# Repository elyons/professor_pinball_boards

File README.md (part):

These are various PCB designs and Gerber files for various applications in Pinball machines.
# professor_pinball_boards

The .sch and .brd files were generated using Autodesk Eagle PCB CAD software: https://www.autodesk.com/products/eagle/free-download

There are .zip files that can be submitted directly to SEEED Fusion for PCB manufacturing: https://www.seeedstudio.com/fusion.html

All boards are released with the Gnu Public License 3.0: https://www.gnu.org/licenses/gpl-3.0.en.html

---

GNU GENERAL PUBLIC LICENSE

Version 3, 29 June 2007

Copyright © 2007 Free Software Foundation, Inc. <https://fsf.org/>

Everyone is permitted to copy and distribute verbatim copies of this license document, but changing it is not allowed.
Preamble

The GNU General Public License is a free, copyleft license for software and other kinds of works.

The licenses for most software and other practical works are designed to take away your freedom to share and change the works. By contrast, the GNU General Public License is intended to guarantee your freedom to share and change all versions of a program--to make sure it remains free software for all its users. We, the Free Software Foundation, use the GNU General Public License for most of our software; it applies also to any other work released this way by its authors. You can apply it to your programs, too.

When we speak of free software, we are referring to freedom, not price. Our General Public Licenses are designed to make sure that you have the freedom to distribute copies of free software (and charge for them if you wish), that you receive source code or can get it if you want it, that you can change the software or use pieces of it in new free programs, and that you know you can do these things.

To protect your rights, we need to prevent others from denying you these rights or asking you to surrender the rights. Therefore, you have certain responsibilities if you distribute copies of the software, or if you modify it: responsibilities to respect the freedom of others.

For example, if you distribute copies of such a program, whether gratis or for a fee, you must pass on to the recipients the same freedoms that you received. You must make sure that they, too, receive or can get the source code. And you must show them these terms so they know their rights.

Developers that use the GNU GPL protect your rights with two steps: (1) assert copyright on the software, and (2) offer you this License giving you legal permission to copy, distribute and/or modify it.

For the developers' and authors' protection, the GPL clearly explains that there is no warranty for this free software. For both users' and authors' sake, the GPL requires that modified versions be marked as changed, so that their problems will not be attributed erroneously to authors of previous versions.

Some devices are designed to deny users access to install or run modified versions of the software inside them, although the manufacturer can do so. This is fundamentally incompatible with the aim of protecting users' freedom to change the software. The systematic pattern of such abuse occurs in the area of products for individuals to use, which is precisely where it is most unacceptable. Therefore, we have designed this version of the GPL to prohibit the practice for those products. If such problems arise substantially in other domains, we stand ready to extend this provision to those domains in future versions of the GPL, as needed to protect the freedom of users.

Finally, every program is threatened constantly by software patents. States should not allow patents to restrict development and use of software on general-purpose computers, but in those that do, we wish to avoid the special danger that patents applied to a free program could make it effectively proprietary. To prevent this, the GPL assures that patents cannot be used to render the program non-free.

The precise terms and conditions for copying, distribution and modification follow.
TERMS AND CONDITIONS
0. Definitions.

“This License” refers to version 3 of the GNU General Public License.

“Copyright” also means copyright-like laws that apply to other kinds of works, such as semiconductor masks.

“The Program” refers to any copyrightable work licensed under this License. Each licensee is addressed as “you”. “Licensees” and “recipients” may be individuals or organizations.

To “modify” a work means to copy from or adapt all or part of the work in a fashion requiring copyright permission, other than the making of an exact copy. The resulting work is called a “modified version” of the earlier work or a work “based on” the earlier work.

A “covered work” means either the unmodified Program or a work based on the Program.

To “propagate” a work means to do anything with it that, without permission, would make you directly or secondarily liable for infringement under applicable copyright law, except executing it on a computer or modifying a private copy. Propagation includes copying, distribution (with or without modification), making available to the public, and in some countries other activities as well.

To “convey” a work means any kind of propagation that enables other parties to make or receive copies. Mere interaction with a user through a computer network, with no transfer of a copy, is not conveying.

An interactive user interface displays “Appropriate Legal Notices” to the extent that it includes a convenient and prominently visible feature that (1) displays an appropriate copyright notice, and (2) tells the user that there is no warranty for the work (except to the extent that warranties are provided), that licensees may convey the work under this License, and how to view a copy of this License. If the interface presents a list of user commands or options, such as a menu, a prominent item in the list meets this criterion.
1. Source Code.

The “source code” for a work means the preferred form of the work for making modifications to it. “Object code” means any non-source form of a work.

A “Standard Interface” means an interface that either is an official standard defined by a recognized standards body, or, in the case of interfaces specified for a particular programming language, one that is widely used among developers working in that language.

The “System Libraries” of an executable work include anything, other than the work as a whole, that (a) is included in the normal form of packaging a Major Component, but which is not part of that Major Component, and (b) serves only to enable use of the work with that Major Component, or to implement a Standard Interface for which an implementation is available to the public in source code form. A “Major Component”, in this context, means a major essential component (kernel, window system, and so on) of the specific operating system (if any) on which the executable work runs, or a compiler used to produce the work, or an object code interpreter used to run it.

The “Corresponding Source” for a work in object code form means all the source code needed to generate, install, and (for an executable work) run the object code and to modify the work, including scripts to control those activities. However, it does not include the work's System Libraries, or general-purpose tools or generally available free programs which are used unmodified in performing those activities but which are not part of the work. For example, Corresponding Source includes interface definition files associated with source files for the work, and the source code for shared libraries and dynamically linked subprograms that the work is specifically designed to require, such as by intimate data communication or control flow between those subprograms and other parts of the work.

The Corresponding Source need not include anything that users can regenerate automatically from other parts of the Corresponding Source.

The Corresponding Source for a work in source code form is that same work.
2. Basic Permissions.

All rights granted under this License are granted for the term of copyright on the Program, and are irrevocable provided the stated conditions are met. This License explicitly affirms your unlimited permission to run the unmodified Program. The output from running a covered work is covered by this License only if the output, given its content, constitutes a covered work. This License acknowledges your rights of fair use or other equivalent, as provided by copyright law.

You may make, run and propagate covered works that you do not convey, without conditions so long as your license otherwise remains in force. You may convey covered works to others for the sole purpose of having them make modifications exclusively for you, or provide you with facilities for running those works, provided that you comply with the terms of this License in conveying all material for which you do not control copyright. Those thus making or running the covered works for you must do so exclusively on your behalf, under your direction and control, on terms that prohibit them from making any copies of your copyrighted material outside their relationship with you.

Conveying under any other circumstances is permitted solely under the conditions stated below. Sublicensing is not allowed; section 10 makes it unnecessary.
3. Protecting Users' Legal Rights From Anti-Circumvention Law.

No covered work shall be deemed part of an effective technological measure under any applicable law fulfilling obligations under article 11 of the WIPO copyright treaty adopted on 20 December 1996, or similar laws prohibiting or restricting circumvention of such measures.

When you convey a covered work, you waive any legal power to forbid circumvention of technological measures to the extent such circumvention is effected by exercising rights under this License with respect to the covered work, and you disclaim any intention to limit operation or modification of the work as a means of enforcing, against the work's users, your or third parties' legal rights to forbid circumvention of technological measures.
4. Conveying Verbatim Copies.

You may convey verbatim copies of the Program's source code as you receive it, in any medium, provided that you conspicuously and appropriately publish on each copy an appropriate copyright notice; keep intact all notices stating that this License and any non-permissive terms added in accord with section 7 apply to the code; keep intact all notices of the absence of any warranty; and give all recipients a copy of this License along with the Program.

You may charge any price or no price for each copy that you convey, and you may offer support or warranty protection for a fee.
5. Conveying Modified Source Versions.

You may convey a work based on the Program, or the modifications to produce it from the Program, in the form of source code under the terms of section 4, provided that you also meet all of these conditions:

    a) The work must carry prominent notices stating that you modified it, and giving a relevant date.
    b) The work must carry prominent notices stating that it is released under this License and any conditions added under section 7. This requirement modifies the requirement in section 4 to “keep intact all notices”.
    c) You must license the entire work, as a whole, under this License to anyone who comes into possession of a copy. This License will therefore apply, along with any applicable section 7 additional terms, to the whole of the work, and all its parts, regardless of how they are packaged. This License gives no permission to license the work in any other way, but it does not invalidate such permission if you have separately received it.
    d) If the work has interactive user interfaces, each must display Appropriate Legal Notices; however, if the Program has interactive interfaces that do not display Appropriate Legal Notices, your work need not make them do so.

A compilation of a covered work with other separate and independent works, which are not by their nature extensions of the covered work, and which are not combined with it such as to form a larger program, in or on a volume of a storage or distribution medium, is called an “aggregate” if the compilation and its resulting copyright are not used to limit the access or legal rights of the compilation's users beyond what the individual works permit. Inclusion of a covered work in an aggregate does not cause this License to apply to the other parts of the aggregate.
6. Conveying Non-Source Forms.

You may convey a covered work in object code form under the terms of sections 4 and 5, provided that you also convey the machine-readable Corresponding Source under the terms of this License, in one of these ways:

    a) Convey the object code in, or embodied in, a physical product (including a physical distribution medium), accompanied by the Corresponding Source fixed on a durable physical medium customarily used for software interchange.
    b) Convey the object code in, or embodied in, a physical product (including a physical distribution medium), accompanied by a written offer, valid for at least three years and valid for as long as you offer spare parts or customer support for that product model, to give anyone who possesses the object code either (1) a copy of the Corresponding Source for all the software in the product that is covered by this License, on a durable physical medium customarily used for software interchange, for a price no more than your reasonable cost of physically performing this conveying of source, or (2) access to copy the Corresponding Source from a network server at no charge.
    c) Convey individual copies of the object code with a copy of the written offer to provide the Corresponding Source. This alternative is allowed only occasionally and noncommercially, and only if you received the object code with such an offer, in accord with subsection 6b.
    d) Convey the object code by offering access from a designated place (gratis or for a charge), and offer equivalent access to the Corresponding Source in the same way through the same place at no further charge. You need not require recipients to copy the Corresponding Source along with the object code. If the place to copy the object code is a network server, the Corresponding Source may be on a different server (operated by you or a third party) that supports equivalent copying facilities, provided you maintain clear directions next to the object code saying where to find the Corresponding Source. Regardless of what server hosts the Corresponding Source, you remain obligated to ensure that it is available for as long as needed to satisfy these requirements.
    e) Convey the object code using peer-to-peer transmission, provided you inform other peers where the object code and Corresponding Source of the work are being offered to the general public at no charge under subsection 6d.

A separable portion of the object code, whose source code is excluded from the Corresponding Source as a System Library, need not be included in conveying the object code work.

A “User Product” is either (1) a “consumer product”, which means any tangible personal property which is normally used for personal, family, or household purposes, or (2) anything designed or sold for incorporation into a dwelling. In determining whether a product is a consumer product, doubtful cases shall be resolved in favor of coverage. For a particular product received by a particular user, “normally used” refers to a typical or common use of that class of product, regardless of the status of the particular user or of the way in which the particular user actually uses, or expects or is expected to use, the product. A product is a consumer product regardless of whether the product has substantial commercial, industrial or non-consumer uses, unless such uses represent the only significant mode of use of the product.

“Installation Information” for a User Product means any methods, procedures, authorization keys, or other information required to install and execute modified versions of a covered work in that User Product from a modified version of its Corresponding Source. The information must suffice to ensure that the continued functioning of the modified object code is in no case prevented or interfered with solely because modification has been made.

If you convey an object code work under this section in, or with, or specifically for use in, a User Product, and the conveying occurs as part of a transaction in which the right of possession and use of the User Product is transferred to the recipient in perpetuity or for a fixed term (regardless of how the transaction is characterized), the Corresponding Source conveyed under this section must be accompanied by the Installation Information. But this requirement does not apply if neither you nor any third party retains the ability to install modified object code on the User Product (for example, the work has been installed in ROM).

The requirement to provide Installation Information does not include a requirement to continue to provide support service, warranty, or updates for a work that has been modified or installed by the recipient, or for the User Product in which it has been modified or installed. Access to a network may be denied when the modification itself materially and adversely affects the operation of the network or violates the rules and protocols for communication across the network.

Corresponding Source conveyed, and Installation Information provided, in accord with this section must be in a format that is publicly documented (and with an implementation available to the public in source code form), and must require no special password or key for unpacking, reading or copying.
7. Additional Terms.

“Additional permissions” are terms that supplement the terms of this License by making exceptions from one or more of its conditions. Additional permissions that are applicable to the entire Program shall be treated as though they were included in this License, to the extent that they are valid under applicable law. If additional permissions apply only to part of the Program, that part may be used separately under those permissions, but the entire Program remains governed by this License without regard to the additional permissions.

When you convey a copy of a covered work, you may at your option remove any additional permissions from that copy, or from any part of it. (Additional permissions may be written to require their own removal in certain cases when you modify the work.) You may place additional permissions on material, added by you to a covered work, for which you have or can give appropriate copyright permission.

Notwithstanding any other provision of this License, for material you add to a covered work, you may (if authorized by the copyright holders of that material) supplement the terms of this License with terms:

    a) Disclaiming warranty or limiting liability differently from the terms of sections 15 and 16 of this License; or
    b) Requiring preservation of specified reasonable legal notices or author attributions in that material or in the Appropriate Legal Notices displayed by works containing it; or
    c) Prohibiting misrepresentation of the origin of that material, or requiring that modified versions of such material be marked in reasonable ways as different from the original version; or
    d) Limiting the use for publicity purposes of names of licensors or authors of the material; or
    e) Declining to grant rights under trademark law for use of some trade names, trademarks, or service marks; or
    f) Requiring indemnification of licensors and authors of that material by anyone who conveys the material (or modified versions of it) with contractual assumptions of liability to the recipient, for any liability that these contractual assumptions directly impose on those licensors and authors.

All other non-permissive additional terms are considered “further restrictions” within the meaning of section 10. If the Program as you received it, or any part of it, contains a notice stating that it is governed by this License along with a term that is a further restriction, you may remove that term. If a license document contains a further restriction but permits relicensing or conveying under this License, you may add to a covered work material governed by the terms of that license document, provided that the further restriction does not survive such relicensing or conveying.

If you add terms to a covered work in accord with this section, you must place, in the relevant source files, a statement of the additional terms that apply to those files, or a notice indicating where to find the applicable terms.

Additional terms, permissive or non-permissive, may be stated in the form of a separately written license, or stated as exceptions; the above requirements apply either way.
8. Termination.

You may not propagate or modify a covered work except as expressly provided under this License. Any attempt otherwise to propagate or modify it is void, and will automatically terminate your rights under this License (including any patent licenses granted under the third paragraph of section 11).

However, if you cease all violation of this License, then your license from a particular copyright holder is reinstated (a) provisionally, unless and until the copyright holder explicitly and finally terminates your license, and (b) permanently, if the copyright holder fails to notify you of the violation by some reasonable means prior to 60 days after the cessation.

Moreover, your license from a particular copyright holder is reinstated permanently if the copyright holder notifies you of the violation by some reasonable means, this is the first time you have received notice of violation of this License (for any work) from that copyright holder, and you cure the violation prior to 30 days after your receipt of the notice.

Termination of your rights under this section does not terminate the licenses of parties who have received copies or rights from you under this License. If your rights have been terminated and not permanently reinstated, you do not qualify to receive new licenses for the same material under section 10.
9. Acceptance Not Required for Having Copies.

You are not required to accept this License in order to receive or run a copy of the Program. Ancillary propagation of a covered work occurring solely as a consequence of using peer-to-peer transmission to receive a copy likewise does not require acceptance. However, nothing other than this License grants you permission to propagate or modify any covered work. These actions infringe copyright if you do not accept this License. Therefore, by modifying or propagating a covered work, you indicate your acceptance of this License to do so.
10. Automatic Licensing of Downstream Recipients.

Each time you convey a covered work, the recipient automatically receives a license from the original licensors, to run, modify and propagate that work, subject to this License. You are not responsible for enforcing compliance by third parties with this License.

An “entity transaction” is a transaction transferring control of an organization, or substantially all assets of one, or subdividing an organization, or merging organizations. If propagation of a covered work results from an entity transaction, each party to that transaction who receives a copy of the work also receives whatever licenses to the work the party's predecessor in interest had or could give under the previous paragraph, plus a right to possession of the Corresponding Source of the work from the predecessor in interest, if the predecessor has it or can get it with reasonable efforts.

You may not impose any further restrictions on the exercise of the rights granted or affirmed under this License. For example, you may not impose a license fee, royalty, or other charge for exercise of rights granted under this License, and you may not initiate litigation (including a cross-claim or counterclaim in a lawsuit) alleging that any patent claim is infringed by making, using, selling, offering for sale, or importing the Program or any portion of it.
11. Patents.

A “contributor” is a copyright holder who authorizes use under this License of the Program or a work on which the Program is based. The work thus licensed is called the contributor's “contributor version”.

A contributor's “essential patent claims” are all patent claims owned or controlled by the contributor, whether already acquired or hereafter acquired, that would be infringed by some manner, permitted by this License, of making, using, or selling its contributor version, but do not include claims that would be infringed only as a consequence of further modification of the contributor version. For purposes of this definition, “control” includes the right to grant patent sublicenses in a manner consistent with the requirements of this License.

Each contributor grants you a non-exclusive, worldwide, royalty-free patent license under the contributor's essential patent claims, to make, use, sell, offer for sale, import and otherwise run, modify and propagate the contents of its contributor version.

In the following three paragraphs, a “patent license” is any express agreement or commitment, however denominated, not to enforce a patent (such as an express permission to practice a patent or covenant not to sue for patent infringement). To “grant” such a patent license to a party means to make such an agreement or commitment not to enforce a patent against the party.

If you convey a covered work, knowingly relying on a patent license, and the Corresponding Source of the work is not available for anyone to copy, free of charge and under the terms of this License, through a publicly available network server or other readily accessible means, then you must either (1) cause the Corresponding Source to be so available, or (2) arrange to deprive yourself of the benefit of the patent license for this particular work, or (3) arrange, in a manner consistent with the requirements of this License, to extend the patent license to downstream recipients. “Knowingly relying” means you have actual knowledge that, but for the patent license, your conveying the covered work in a country, or your recipient's use of the covered work in a country, would infringe one or more identifiable patents in that country that you have reason to believe are valid.

If, pursuant to or in connection with a single transaction or arrangement, you convey, or propagate by procuring conveyance of, a covered work, and grant a patent license to some of the parties receiving the covered work authorizing them to use, propagate, modify or convey a specific copy of the covered work, then the patent license you grant is automatically extended to all recipients of the covered work and works based on it.

A patent license is “discriminatory” if it does not include within the scope of its coverage, prohibits the exercise of, or is conditioned on the non-exercise of one or more of the rights that are specifically granted under this License. You may not convey a covered work if you are a party to an arrangement with a third party that is in the business of distributing software, under which you make payment to the third party based on the extent of your activity of conveying the work, and under which the third party grants, to any of the parties who would receive the covered work from you, a discriminatory patent license (a) in connection with copies of the covered work conveyed by you (or copies made from those copies), or (b) primarily for and in connection with specific products or compilations that contain the covered work, unless you entered into that arrangement, or that patent license was granted, prior to 28 March 2007.

Nothing in this License shall be construed as excluding or limiting any implied license or other defenses to infringement that may otherwise be available to you under applicable patent law.
12. No Surrender of Others' Freedom.

If conditions are imposed on you (whether by court order, agreement or otherwise) that contradict the conditions of this License, they do not excuse you from the conditions of this License. If you cannot convey a covered work so as to satisfy simultaneously your obligations under this License and any other pertinent obligations, then as a consequence you may not convey it at all. For example, if you agree to terms that obligate you to collect a royalty for further conveying from those to whom you convey the Program, the only way you could satisfy both those terms and this License would be to refrain entirely from conveying the Program.
13. Use with the GNU Affero General Public License.

Notwithstanding any other provision of this License, you have permission to link or combine any covered work with a work licensed under version 3 of the GNU Affero General Public License into a single combined work, and to convey the resulting work. The terms of this License will continue to apply to the part which is the covered work, but the special requirements of the GNU Affero General Public License, section 13, concerning interaction through a network will apply to the combination as such.
14. Revised Versions of this License.

The Free Software Foundation may publish revised and/or new versions of the GNU General Public License from time to time. Such new versions will be similar in spirit to the present version, but may differ in detail to address new problems or concerns.

Each version is given a distinguishing version number. If the Program specifies that a certain numbered version of the GNU General Public License “or any later version” applies to it, you have the option of following the terms and conditions either of that numbered version or of any later version published by the Free Software Foundation. If the Program does not specify a version number of the GNU General Public License, you may choose any version ever published by the Free Software Foundation.

If the Program specifies that a proxy can decide which future versions of the GNU General Public License can be used, that proxy's public statement of acceptance of a version permanently authorizes you to choose that version for the Program.

Later license versions may give you additional or different permissions. However, no additional obligations are imposed on any author or copyright holder as a result of your choosing to follow a later version.
15. Disclaimer of Warranty.

THERE IS NO WARRANTY FOR THE PROGRAM, TO THE EXTENT PERMITTED BY APPLICABLE LAW. EXCEPT WHEN OTHERWISE STATED IN WRITING THE COPYRIGHT HOLDERS AND/OR OTHER PARTIES PROVIDE THE PROGRAM “AS IS” WITHOUT WARRANTY OF ANY KIND, EITHER EXPRESSED OR IMPLIED, INCLUDING, BUT NOT LIMITED TO, THE IMPLIED WARRANTIES OF MERCHANTABILITY AND FITNESS FOR A PARTICULAR PURPOSE. THE ENTIRE RISK AS TO THE QUALITY AND PERFORMANCE OF THE PROGRAM IS WITH YOU. SHOULD THE PROGRAM PROVE DEFECTIVE, YOU ASSUME THE COST OF ALL NECESSARY SERVICING, REPAIR OR CORRECTION.
16. Limitation of Liability.

IN NO EVENT UNLESS REQUIRED BY APPLICABLE LAW OR AGREED TO IN WRITING WILL ANY COPYRIGHT HOLDER, OR ANY OTHER PARTY WHO MODIFIES AND/OR CONVEYS THE PROGRAM AS PERMITTED ABOVE, BE LIABLE TO YOU FOR DAMAGES, INCLUDING ANY GENERAL, SPECIAL, INCIDENTAL OR CONSEQUENTIAL DAMAGES ARISING OUT OF THE USE OR INABILITY TO USE THE PROGRAM (INCLUDING BUT NOT LIMITED TO LOSS OF DATA OR DATA BEING RENDERED INACCURATE OR LOSSES SUSTAINED BY YOU OR THIRD PARTIES OR A FAILURE OF THE PROGRAM TO OPERATE WITH ANY OTHER PROGRAMS), EVEN IF SUCH HOLDER OR OTHER PARTY HAS BEEN ADVISED OF THE POSSIBILITY OF SUCH DAMAGES.
17. Interpretation of Sections 15 and 16.

If the disclaimer of warranty and limitation of liability provided above cannot be given local legal effect according to their terms, reviewing courts shall apply local law that most closely approximates an absolute waiver of all civil liability in connection with the Program, unless a warranty or assumption of liability accompanies a copy of the Program in return for a fee.

END OF TERMS AND CONDITIONS
How to Apply These Terms to Your New Programs

If you develop a new program, and you want it to be of the greatest possible use to the public, the best way to achieve this is to make it free software which everyone can redistribute and change under these terms.

To do so, attach the following notices to the program. It is safest to attach them to the start of each source file to most effectively state the exclusion of warranty; and each file should have at least the “copyright” line and a pointer to where the full notice is found.

    <one line to give the program's name and a brief idea of what it does.>
    Copyright (C) <year>  <name of author>

    This program is free software: you can redistribute it and/or modify
    it under the terms of the GNU General Public License as published by
    the Free Software Foundation, either version 3 of the License, or
    (at your option) any later version.

    This program is distributed in the hope that it will be useful,
    but WITHOUT ANY WARRANTY; without even the implied warranty of
    MERCHANTABILITY or FITNESS FOR A PARTICULAR PURPOSE.  See the
    GNU General Public License for more details.

    You should have received a copy of the GNU General Public License
    along with this program.  If not, see <https://www.gnu.org/licenses/>.

Also add information on how to contact you by electronic and paper mail.

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
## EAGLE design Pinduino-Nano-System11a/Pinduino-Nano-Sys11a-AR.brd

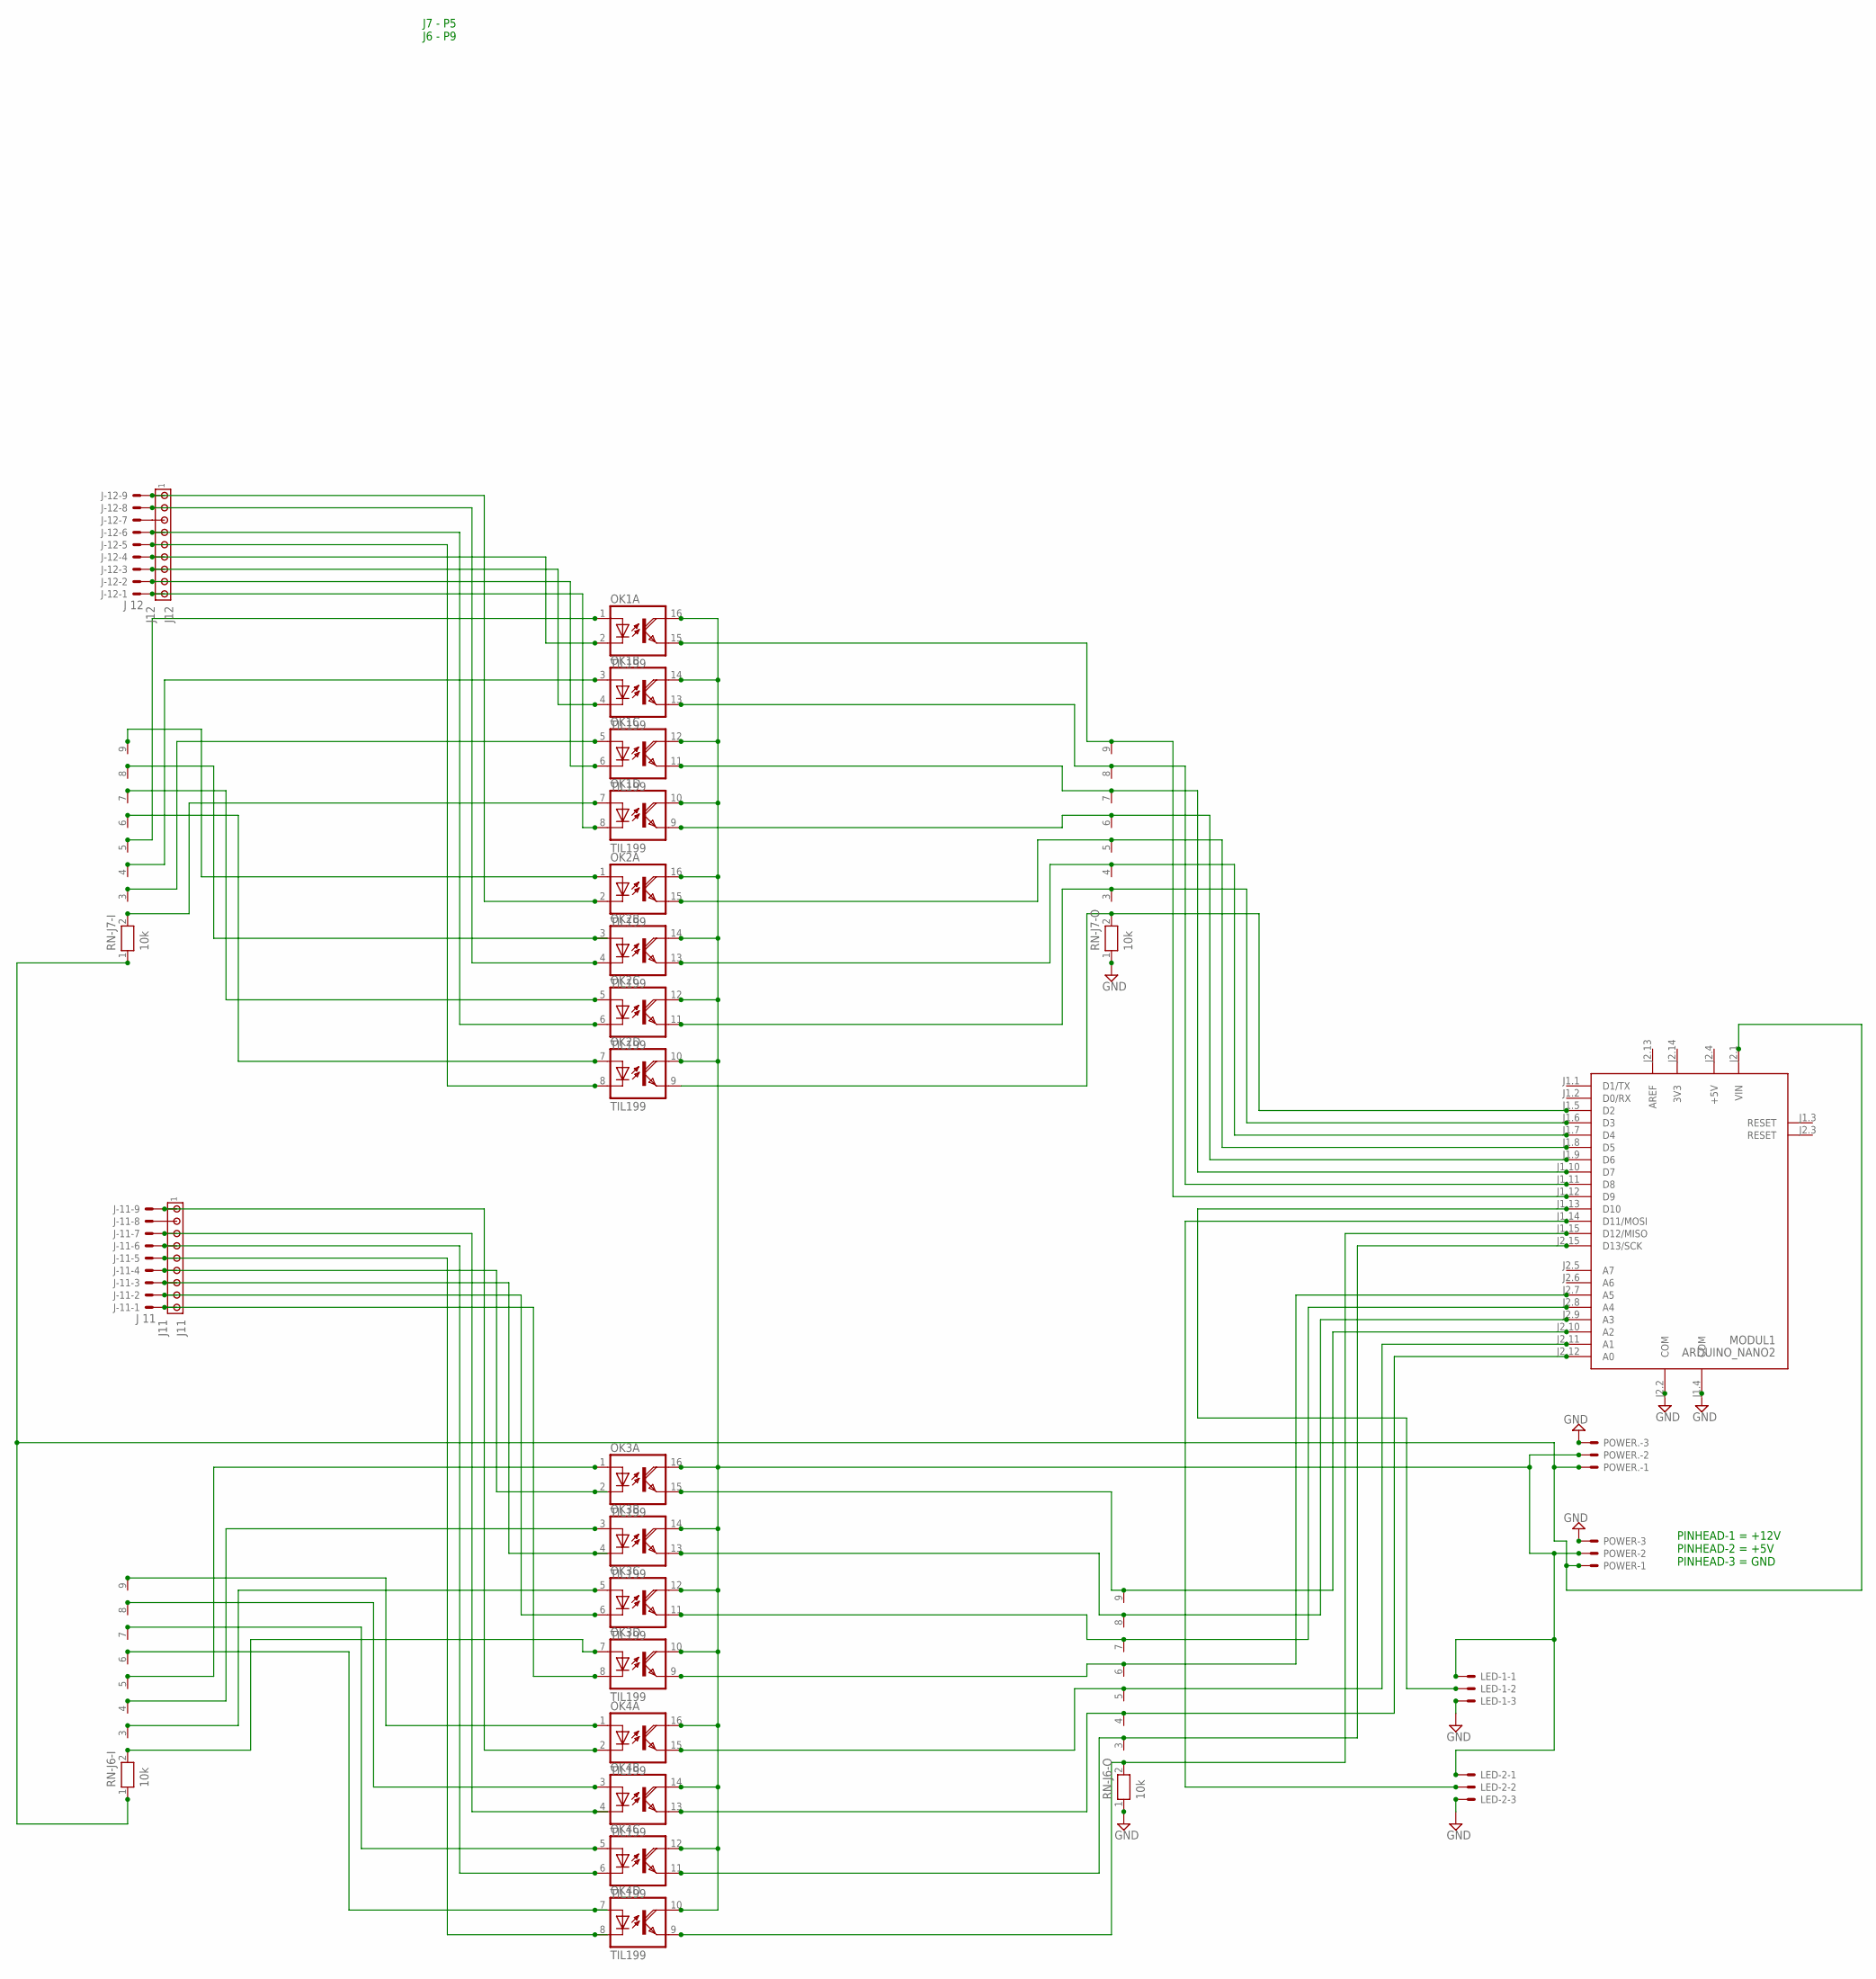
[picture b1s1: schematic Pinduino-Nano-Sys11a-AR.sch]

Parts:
J11: J11; 1X9MTA
J12: J12; 1X9MTA
J-11: J 11; KK-156-9
J-12: J 12; KK-156-9
LED-1, LED-2: 22-23-2031
MODUL1: ARDUINO_NANO2
OK1, OK2, OK3, OK4: TIL199; DIL16
POWER, POWER.: 22-23-2031
RN-J6-I, RN-J6-O, RN-J7-I, RN-J7-O: 10k; RN-9

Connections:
3V3: MODUL1.J2.14 (3V3)
+5V: MODUL1.J2.4 (+5V)
ARD+5V: LED-1.1, LED-2.1, OK1.10 (COL), OK1.12 (COL), OK1.14 (COL), OK1.16 (COL), OK2.10 (COL), OK2.12 (COL), OK2.14 (COL), OK2.16 (COL), OK3.10 (COL), OK3.12 (COL), OK3.14 (COL), OK3.16 (COL), OK4.10 (COL), OK4.12 (COL), OK4.14 (COL), OK4.16 (COL), POWER.2, POWER..2
AREF: MODUL1.J2.13 (AREF)
GND: LED-1.3, LED-2.3, MODUL1.J1.4 (COM), MODUL1.J2.2 (COM), POWER.3, POWER..3, RN-J6-O.1, RN-J7-O.1
unnamed: J12.6, J-12.4, OK1.2 (C)
unnamed: MODUL1.J1.5 (D2), OK2.9 (EMI), RN-J7-O.2
unnamed: OK1.3 (A), RN-J7-I.4
unnamed: OK1.5 (A), RN-J7-I.3
unnamed: OK1.7 (A), RN-J7-I.2
unnamed: OK2.1 (A), RN-J7-I.9
unnamed: OK2.3 (A), RN-J7-I.8
unnamed: OK2.5 (A), RN-J7-I.7
unnamed: OK1.1 (A), RN-J7-I.5
unnamed: J12.9, J-12.1, OK1.8 (C)
unnamed: J12.8, J-12.2, OK1.6 (C)
unnamed: J12.7, J-12.3, OK1.4 (C)
unnamed: OK2.7 (A), RN-J7-I.6
unnamed: J12.5, J-12.5, OK2.8 (C)
unnamed: J11.9, J-11.1, OK3.8 (C)
unnamed: J12.2, J-12.8, OK2.4 (C)
unnamed: J12.1, J-12.9, OK2.2 (C)
unnamed: MODUL1.J1.6 (D3), OK2.11 (EMI), RN-J7-O.3
unnamed: J11.7, J-11.3, OK3.4 (C)
unnamed: J11.5, J-11.5, OK4.8 (C)
unnamed: J11.4, J-11.6, OK4.6 (C)
unnamed: J11.3, J-11.7, OK4.4 (C)
unnamed: J12.3, J-12.7
unnamed: MODUL1.J1.11 (D8), OK1.13 (EMI), RN-J7-O.8
unnamed: J11.2, J-11.8
unnamed: J11.1, J-11.9, OK4.2 (C)
unnamed: MODUL1.J1.7 (D4), OK2.13 (EMI), RN-J7-O.4
unnamed: OK4.1 (A), RN-J6-I.9
unnamed: OK4.3 (A), RN-J6-I.8
unnamed: OK4.5 (A), RN-J6-I.7
unnamed: OK3.3 (A), RN-J6-I.4
unnamed: OK3.1 (A), RN-J6-I.5
unnamed: OK3.5 (A), RN-J6-I.3
unnamed: OK4.7 (A), RN-J6-I.6
unnamed: MODUL1.J2.8 (A4), OK3.11 (EMI), RN-J6-O.7
unnamed: OK3.7 (A), RN-J6-I.2
unnamed: MODUL1.J2.7 (A5), OK3.9 (EMI), RN-J6-O.6
unnamed: MODUL1.J2.15 (D13/SCK), OK4.11 (EMI), RN-J6-O.3
unnamed: J11.8, J-11.2, OK3.6 (C)
unnamed: MODUL1.J2.12 (A0), OK4.13 (EMI), RN-J6-O.4
unnamed: MODUL1.J2.11 (A1), OK4.15 (EMI), RN-J6-O.5
unnamed: LED-2.2, MODUL1.J1.14 (D11/MOSI)
unnamed: LED-1.2, MODUL1.J1.13 (D10)
unnamed: MODUL1.J1.12 (D9), OK1.15 (EMI), RN-J7-O.9
unnamed: J12.4, J-12.6, OK2.6 (C)
unnamed: J11.6, J-11.4, OK3.2 (C)
unnamed: MODUL1.J1.10 (D7), OK1.11 (EMI), RN-J7-O.7
unnamed: MODUL1.J1.8 (D5), OK2.15 (EMI), RN-J7-O.5
unnamed: MODUL1.J1.9 (D6), OK1.9 (EMI), RN-J7-O.6
unnamed: MODUL1.J2.9 (A3), OK3.13 (EMI), RN-J6-O.8
unnamed: MODUL1.J2.10 (A2), OK3.15 (EMI), RN-J6-O.9
unnamed: MODUL1.J1.15 (D12/MISO), OK4.9 (EMI), RN-J6-O.2
unnamed: MODUL1.J2.1 (VIN), POWER.1, POWER..1, RN-J6-I.1, RN-J7-I.1

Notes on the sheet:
J7 - P5 J6 - P9
PINHEAD-1 = +12V PINHEAD-2 = +5V PINHEAD-3 = GND

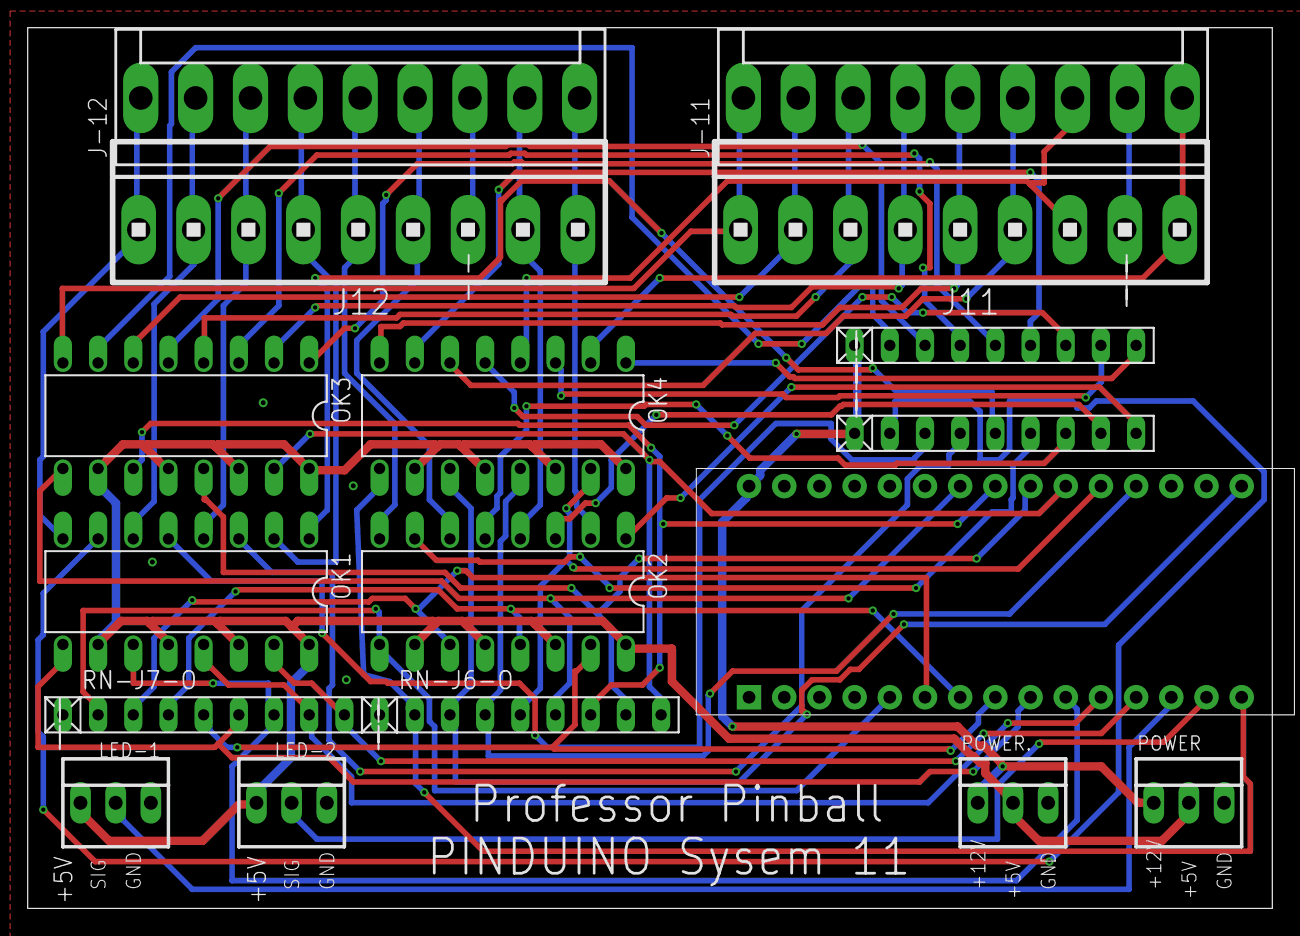
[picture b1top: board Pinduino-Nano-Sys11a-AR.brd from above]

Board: 2 copper layers, 89.8 x 63.6 mm, 17 parts (0 on the bottom side), 55 nets.

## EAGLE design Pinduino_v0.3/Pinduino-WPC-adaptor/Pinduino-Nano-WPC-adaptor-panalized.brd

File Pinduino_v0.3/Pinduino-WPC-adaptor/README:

Probably use the "wide" version for updates to the SEEED requirements for manufacturing

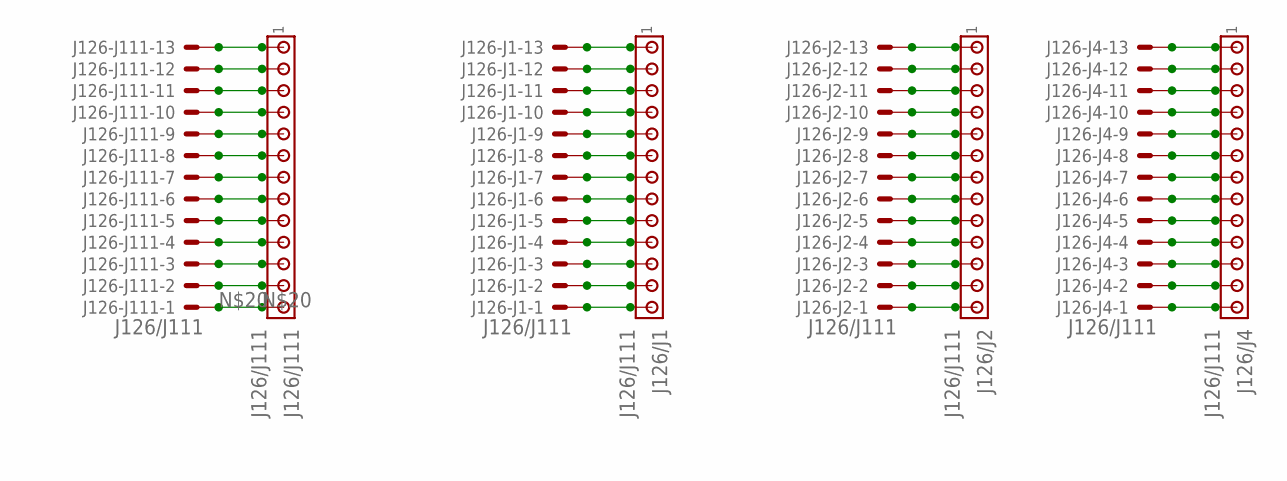
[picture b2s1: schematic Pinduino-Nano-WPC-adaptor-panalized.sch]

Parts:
J126-J1, J126-J2, J126-J4, J126-J111: J126/J111; KK-156-13
J126/J1, J126/J2, J126/J4, J126/J111: J126/J111; 1X13MTA

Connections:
unnamed: J126-J1.12, J126/J1.2
unnamed: J126-J1.13, J126/J1.1
unnamed: J126-J1.9, J126/J1.5
unnamed: J126-J1.5, J126/J1.9
unnamed: J126-J1.6, J126/J1.8
unnamed: J126-J1.7, J126/J1.7
unnamed: J126-J1.8, J126/J1.6
unnamed: J126-J1.10, J126/J1.4
unnamed: J126-J1.11, J126/J1.3
unnamed: J126-J1.4, J126/J1.10
unnamed: J126-J1.3, J126/J1.11
unnamed: J126-J1.2, J126/J1.12
unnamed: J126-J1.1, J126/J1.13
unnamed: J126-J2.12, J126/J2.2
unnamed: J126-J2.13, J126/J2.1
unnamed: J126-J2.9, J126/J2.5
unnamed: J126-J2.5, J126/J2.9
unnamed: J126-J2.6, J126/J2.8
unnamed: J126-J111.3, J126/J111.11
unnamed: J126-J111.2, J126/J111.12
unnamed: J126-J111.12, J126/J111.2
unnamed: J126-J111.13, J126/J111.1
unnamed: J126-J111.4, J126/J111.10
unnamed: J126-J2.7, J126/J2.7
unnamed: J126-J111.1, J126/J111.13
unnamed: J126-J2.8, J126/J2.6
unnamed: J126-J111.9, J126/J111.5
unnamed: J126-J2.10, J126/J2.4
unnamed: J126-J2.11, J126/J2.3
unnamed: J126-J2.4, J126/J2.10
unnamed: J126-J2.3, J126/J2.11
unnamed: J126-J2.2, J126/J2.12
unnamed: J126-J2.1, J126/J2.13
unnamed: J126-J4.12, J126/J4.2
unnamed: J126-J4.13, J126/J4.1
unnamed: J126-J4.9, J126/J4.5
unnamed: J126-J4.5, J126/J4.9
unnamed: J126-J4.6, J126/J4.8
unnamed: J126-J4.7, J126/J4.7
unnamed: J126-J4.8, J126/J4.6
unnamed: J126-J4.10, J126/J4.4
unnamed: J126-J4.11, J126/J4.3
unnamed: J126-J4.4, J126/J4.10
unnamed: J126-J4.3, J126/J4.11
unnamed: J126-J111.6, J126/J111.8
unnamed: J126-J111.7, J126/J111.7
unnamed: J126-J4.2, J126/J4.12
unnamed: J126-J4.1, J126/J4.13
unnamed: J126-J111.8, J126/J111.6
unnamed: J126-J111.5, J126/J111.9
unnamed: J126-J111.10, J126/J111.4
unnamed: J126-J111.11, J126/J111.3

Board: 2 copper layers, 8 parts (0 on the bottom side), 52 nets, no tracks yet.

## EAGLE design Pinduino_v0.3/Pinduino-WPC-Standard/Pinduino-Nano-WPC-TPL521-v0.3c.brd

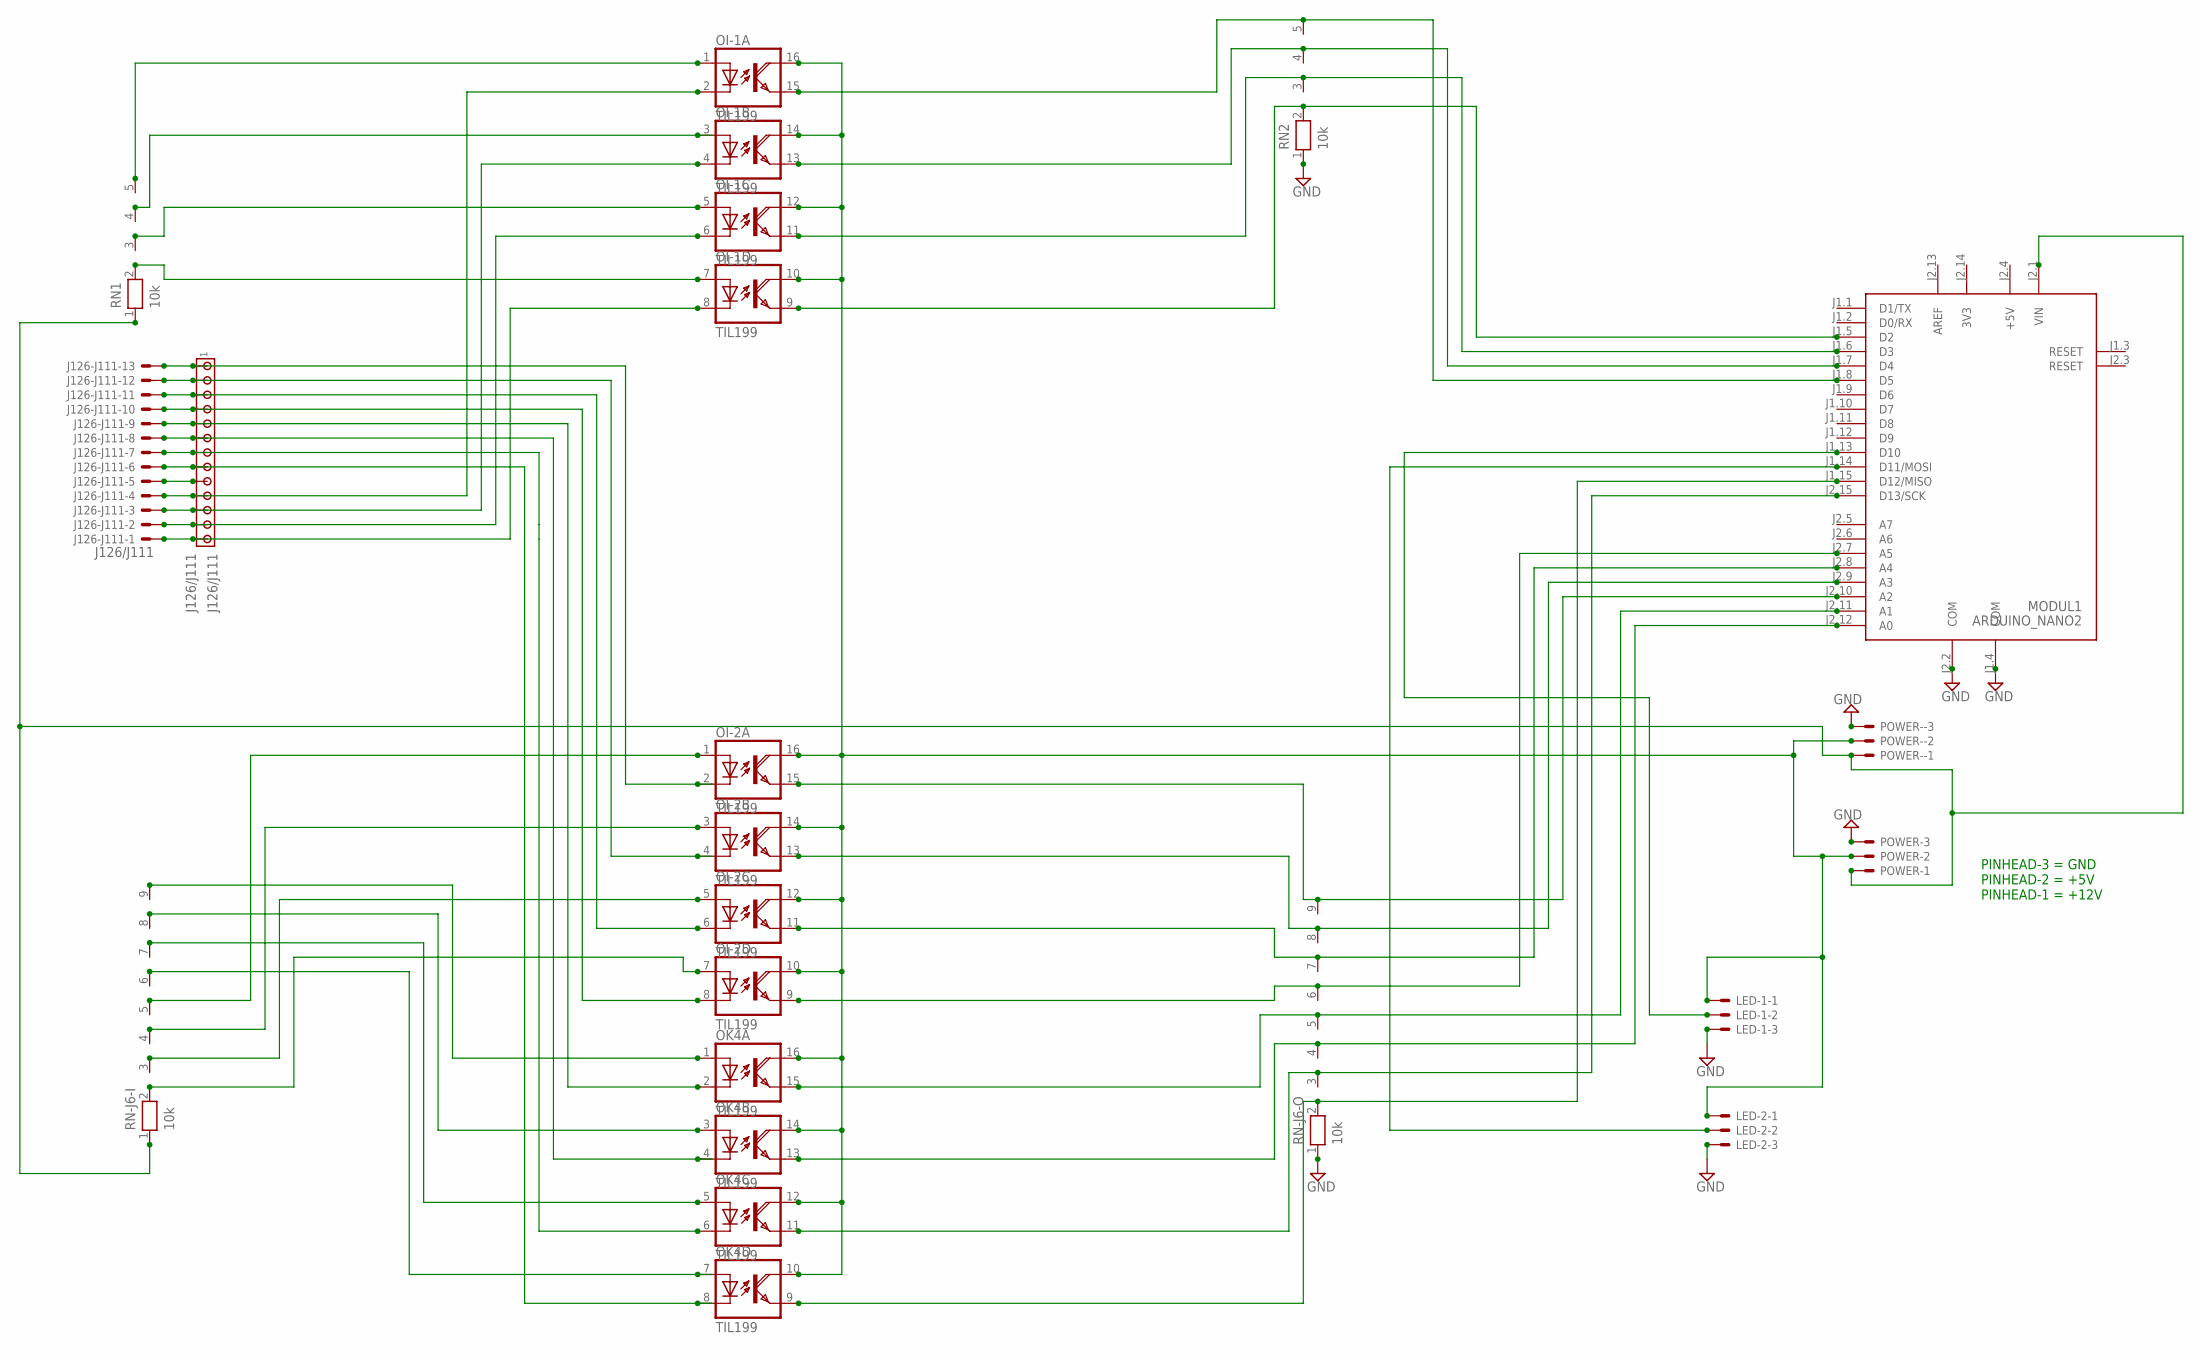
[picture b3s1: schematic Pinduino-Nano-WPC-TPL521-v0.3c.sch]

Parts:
J126-J111: J126/J111; KK-156-13
J126/J111: J126/J111; 1X13MTA
LED-1, LED-2: 22-23-2031
MODUL1: ARDUINO_NANO2
OI-1, OI-2: TIL199; DIL16
OK4: TIL199; DIL16
POWER: 22-23-2031
POWER-: 22-23-2031
RN1, RN2: 10k; RN-5
RN-J6-I, RN-J6-O: 10k; RN-9

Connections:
3V3: MODUL1.J2.14 (3V3)
+5V: MODUL1.J2.4 (+5V)
ARD+5V: LED-1.1, LED-2.1, OI-1.10 (COL), OI-1.12 (COL), OI-1.14 (COL), OI-1.16 (COL), OI-2.10 (COL), OI-2.12 (COL), OI-2.14 (COL), OI-2.16 (COL), OK4.10 (COL), OK4.12 (COL), OK4.14 (COL), OK4.16 (COL), POWER.2, POWER-.2
AREF: MODUL1.J2.13 (AREF)
GND: LED-1.3, LED-2.3, MODUL1.J1.4 (COM), MODUL1.J2.2 (COM), POWER.3, POWER-.3, RN2.1, RN-J6-O.1
unnamed: MODUL1.J2.1 (VIN), POWER.1, POWER-.1, RN1.1, RN-J6-I.1
unnamed: MODUL1.J1.5 (D2), OI-1.9 (EMI), RN2.2
unnamed: OI-1.5 (A), RN1.3
unnamed: OI-1.1 (A), RN1.5
unnamed: OI-1.3 (A), RN1.4
unnamed: OI-1.7 (A), RN1.2
unnamed: MODUL1.J1.6 (D3), OI-1.11 (EMI), RN2.3
unnamed: J126-J111.3, J126/J111.11, OI-1.4 (C)
unnamed: J126-J111.2, J126/J111.12, OI-1.6 (C)
unnamed: J126-J111.12, J126/J111.2, OI-2.4 (C)
unnamed: J126-J111.13, J126/J111.1, OI-2.2 (C)
unnamed: J126-J111.4, J126/J111.10, OI-1.2 (C)
unnamed: J126-J111.1, J126/J111.13, OI-1.8 (C)
unnamed: J126-J111.9, J126/J111.5, OK4.2 (C)
unnamed: MODUL1.J1.7 (D4), OI-1.13 (EMI), RN2.4
unnamed: OK4.1 (A), RN-J6-I.9
unnamed: OK4.3 (A), RN-J6-I.8
unnamed: OK4.5 (A), RN-J6-I.7
unnamed: OI-2.3 (A), RN-J6-I.4
unnamed: OI-2.1 (A), RN-J6-I.5
unnamed: OI-2.5 (A), RN-J6-I.3
unnamed: OK4.7 (A), RN-J6-I.6
unnamed: MODUL1.J2.8 (A4), OI-2.11 (EMI), RN-J6-O.7
unnamed: OI-2.7 (A), RN-J6-I.2
unnamed: MODUL1.J2.7 (A5), OI-2.9 (EMI), RN-J6-O.6
unnamed: MODUL1.J2.15 (D13/SCK), OK4.11 (EMI), RN-J6-O.3
unnamed: MODUL1.J2.12 (A0), OK4.13 (EMI), RN-J6-O.4
unnamed: MODUL1.J2.11 (A1), OK4.15 (EMI), RN-J6-O.5
unnamed: LED-2.2, MODUL1.J1.14 (D11/MOSI)
unnamed: LED-1.2, MODUL1.J1.13 (D10)
unnamed: MODUL1.J1.8 (D5), OI-1.15 (EMI), RN2.5
unnamed: MODUL1.J2.9 (A3), OI-2.13 (EMI), RN-J6-O.8
unnamed: MODUL1.J2.10 (A2), OI-2.15 (EMI), RN-J6-O.9
unnamed: J126-J111.6, J126/J111.8, OK4.8 (C)
unnamed: J126-J111.7, J126/J111.7, OK4.6 (C)
unnamed: MODUL1.J1.15 (D12/MISO), OK4.9 (EMI), RN-J6-O.2
unnamed: J126-J111.8, J126/J111.6, OK4.4 (C)
unnamed: J126-J111.5, J126/J111.9
unnamed: J126-J111.10, J126/J111.4, OI-2.8 (C)
unnamed: J126-J111.11, J126/J111.3, OI-2.6 (C)

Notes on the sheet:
PINHEAD-3 = GND PINHEAD-2 = +5V PINHEAD-1 = +12V

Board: 2 copper layers, 14 parts (0 on the bottom side), 42 nets, no tracks yet.

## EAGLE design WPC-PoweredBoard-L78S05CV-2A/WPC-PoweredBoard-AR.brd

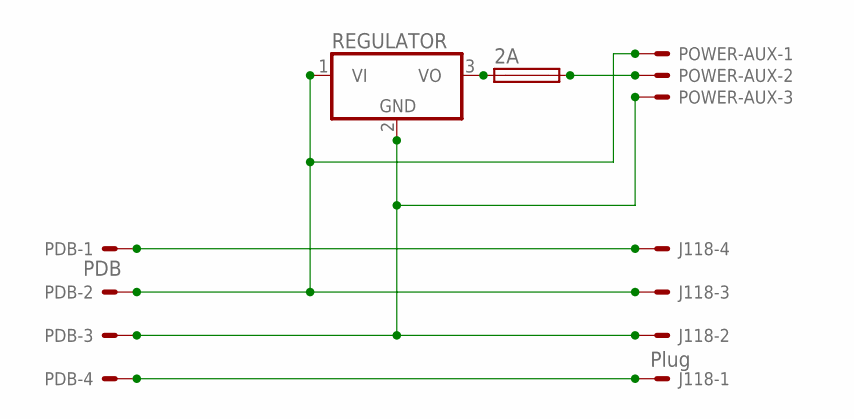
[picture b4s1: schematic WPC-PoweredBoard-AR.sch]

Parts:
2A: FUSESHK20L; SHK20L
J118: Plug; KK-156-4
PDB: PDB; KK-156-4
POWER-AUX: 22-23-2031
REGULATOR: 786TV; TO220V

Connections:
unnamed: J118.1, PDB.4
unnamed: J118.3, PDB.2, POWER-AUX.1, REGULATOR.1 (VI)
unnamed: J118.2, PDB.3, POWER-AUX.3, REGULATOR.2 (GND)
unnamed: 2A.2A (2), POWER-AUX.2
unnamed: 2A.1A (1), REGULATOR.3 (VO)
unnamed: J118.4, PDB.1

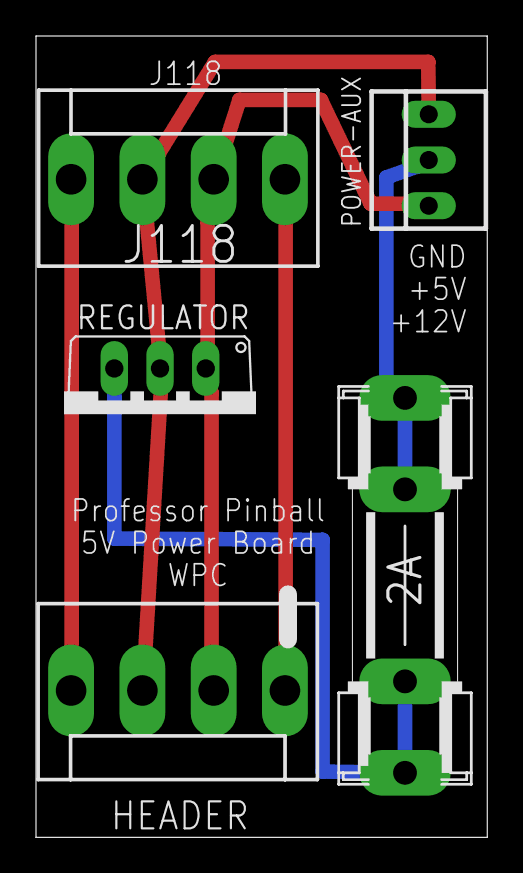
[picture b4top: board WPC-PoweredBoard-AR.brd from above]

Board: 2 copper layers, 25.1 x 44.5 mm, 5 parts (0 on the bottom side), 6 nets.

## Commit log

2017-07-29 initial import
2017-07-29 importing images of board
2017-07-29 updated 'software' to 'design'
2017-08-21 moving Pinduino v0.2 board files here.
2024-03-29 added board files for the WPC power board and WPC V0.3 Pinduino boards (standard and extended)
2024-03-29 added board files
2025-04-23 added board files for Pinduino used in sys 11
2025-04-23 moved board files to appropriate location

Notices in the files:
README.md:
If a license document contains a further restriction but permits relicensing or conveying under this License, you may add to a covered work material governed by the terms of that license document, provided that the further restriction does not survive such relicensing or conveying.
You may not propagate or modify a covered work except as expressly provided under this License. Any attempt otherwise to propagate or modify it is void, and will automatically terminate your rights under this License (including any patent licenses granted under the third paragraph of section 11).
